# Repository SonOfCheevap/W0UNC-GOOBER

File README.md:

# W0UNC-GOOBER
Project for W0UNC for making off grid communication nodes

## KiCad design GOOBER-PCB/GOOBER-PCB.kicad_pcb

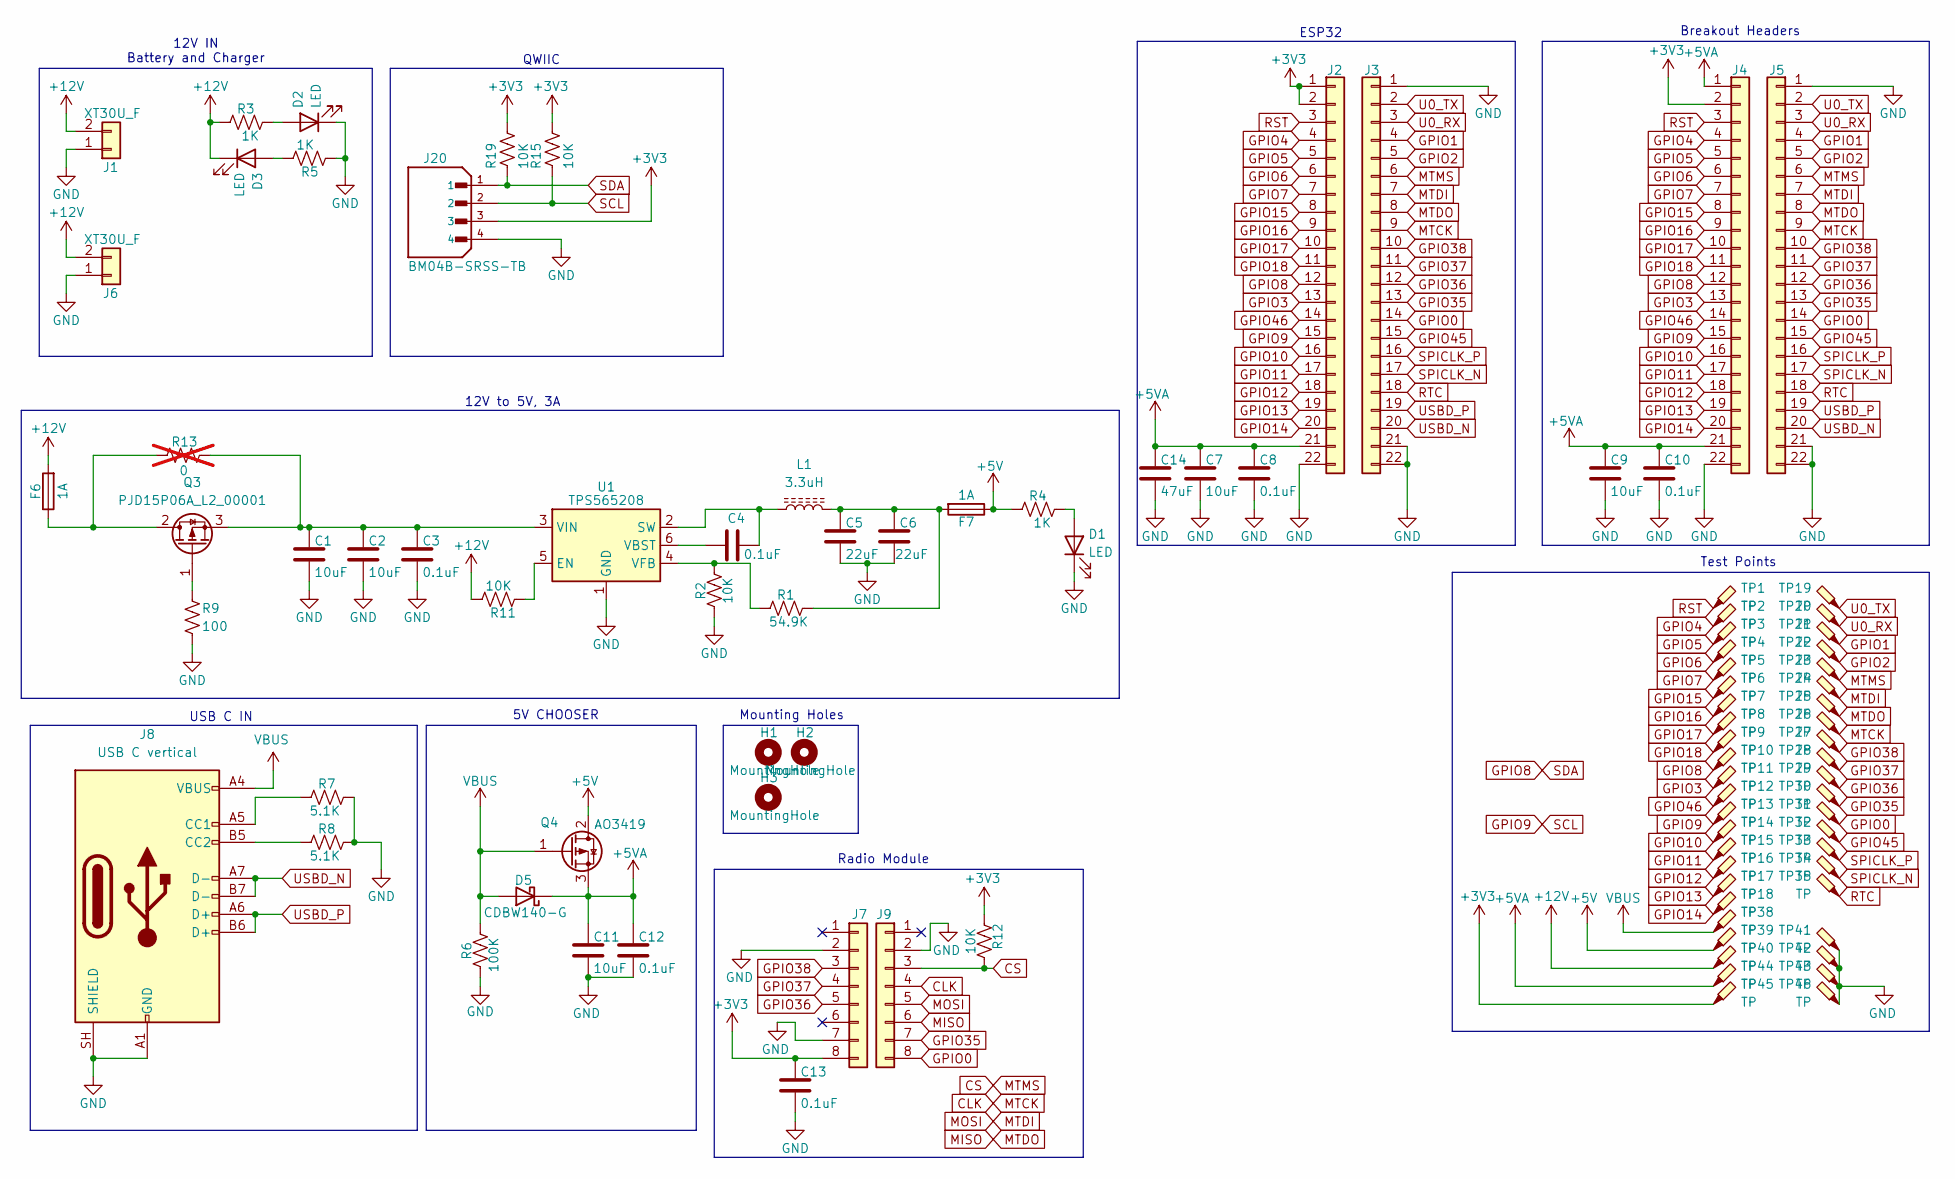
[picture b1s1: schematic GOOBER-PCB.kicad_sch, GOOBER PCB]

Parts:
C1, C2, C7, C9, C11: 10uF; C_0805_2012Metric_Pad1.18x1.45mm_HandSolder
C3, C4, C8, C10, C12, C13: 0.1uF; C_0805_2012Metric_Pad1.18x1.45mm_HandSolder
C5, C6: 22uF; C_0805_2012Metric_Pad1.18x1.45mm_HandSolder
C14: 47uF; C_1206_3216Metric_Pad1.33x1.80mm_HandSolder
D1, D2, D3: LED; LED_0805_2012Metric
D5: CDBW140-G; D_SOD-123
F6, F7: 1A; Fuseholder_Blade_Mini_Keystone_3568
H1, H2, H3: MountingHole; MountingHole_3.2mm_M3_ISO7380
J1, J6: XT30U_F; AMASS_XT30PW-M_1x02_P2.50mm_Horizontal
J2, J3, J4, J5: Conn_01x22; PinHeader_1x22_P2.54mm_Vertical
J7, J9: Conn_01x08; PinHeader_1x08_P2.54mm_Vertical
J8: USB C vertical; USB_C_Receptacle_GCT_USB4115-03-C
J20: BM04B-SRSS-TB; JST_SH_BM04B-SRSS-TB_1x04-1MP_P1.00mm_Vertical; PARTREV NA
L1: 3.3uH; L_TDK_VLS6045EX_VLS6045AF
Q3: PJD15P06A_L2_00001; TO-252-2
Q4: AO3419; SOT-23_Handsoldering
R1: 54.9K; R_0805_2012Metric_Pad1.20x1.40mm_HandSolder
R2, R11, R12, R15, R19: 10K; R_0805_2012Metric_Pad1.20x1.40mm_HandSolder
R3, R4, R5: 1K; R_0805_2012Metric_Pad1.20x1.40mm_HandSolder
R6: 100K; R_0805_2012Metric_Pad1.20x1.40mm_HandSolder
R7, R8: 5.1K; R_0805_2012Metric_Pad1.20x1.40mm_HandSolder
R9: 100; R_0805_2012Metric_Pad1.20x1.40mm_HandSolder
R13: 0; R_1210_3225Metric_Pad1.30x2.65mm_HandSolder; not fitted
TP1, TP2, TP3, TP4, TP5, TP6, TP7, TP8, TP9, TP10, TP11, TP12, TP13, TP14, TP15, TP16, TP17, TP18, TP19, TP20, TP21, TP22, TP23, TP24, TP25, TP26, TP27, TP28, TP29, TP30, TP31, TP32, TP33, TP34, TP35, TP38, TP39, TP40, TP41, TP42, TP43, TP44, TP45, TP46: TP; TestPoint_Keystone_5000-5004_Miniature
U1: TPS565208; SOT-23-6

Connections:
+3V3: C13.1, J2.1, J2.2, J4.2, J7.8, J20.3, R12.1, R15.2, R19.2, TP45.1 (1_1)
+5V: F7.1, Q4.2 (D), R4.1, TP39.1 (1_1)
+5VA: C7.1, C8.1, C9.1, C10.1, C11.1, C12.1, C14.1, D5.1 (K), J2.21, J4.1, J4.21, Q4.3 (S), TP44.1 (1_1)
+12V: D3.1 (K), F6.2, J1.2, J6.2, R3.1, R11.2, TP40.1 (1_1)
CLK: J3.9, J5.9, J9.4, TP26.1 (1_1)
CS: J3.6, J5.6, J9.3, R12.2, TP23.1 (1_1)
GND: C1.2, C2.2, C3.2, C5.2, C6.2, C7.2, C8.2, C9.2, C10.2, C11.2, C12.2, C13.2, C14.2, D1.1 (K), D2.1 (K), J1.1, J2.22, J3.1, J3.21, J3.22, J4.22, J5.1, J5.21, J5.22, J6.1, J7.2, J7.7, J8.A1 (GND), J8.A12 (GND), J8.B1 (GND), J8.B12 (GND), J8.SH (SHIELD), J9.2, J20.4, R2.1, R5.1, R6.1, R7.2, R8.2, R9.2, TP41.1 (1_1), TP42.1 (1_1), TP43.1 (1_1), TP46.1 (1_1), U1.1 (GND)
GPIO0: J3.14, J5.14, J9.8, TP31.1 (1_1)
GPIO1: J3.4, J5.4, TP21.1 (1_1)
GPIO2: J3.5, J5.5, TP22.1 (1_1)
GPIO3: J2.13, J4.13, TP11.1 (1_1)
GPIO4: J2.4, J4.4, TP2.1 (1_1)
GPIO5: J2.5, J4.5, TP3.1 (1_1)
GPIO6: J2.6, J4.6, TP4.1 (1_1)
GPIO7: J2.7, J4.7, TP5.1 (1_1)
GPIO8: J2.12, J4.12, J20.1, R19.1, TP10.1 (1_1)
GPIO9: J2.15, J4.15, J20.2, R15.1, TP13.1 (1_1)
GPIO10: J2.16, J4.16, TP14.1 (1_1)
GPIO11: J2.17, J4.17, TP15.1 (1_1)
GPIO12: J2.18, J4.18, TP16.1 (1_1)
GPIO13: J2.19, J4.19, TP17.1 (1_1)
GPIO14: J2.20, J4.20, TP18.1 (1_1)
GPIO15: J2.8, J4.8, TP6.1 (1_1)
GPIO16: J2.9, J4.9, TP7.1 (1_1)
GPIO17: J2.10, J4.10, TP8.1 (1_1)
GPIO18: J2.11, J4.11, TP9.1 (1_1)
GPIO35: J3.13, J5.13, J9.7, TP30.1 (1_1)
GPIO36: J3.12, J5.12, J7.5, TP29.1 (1_1)
GPIO37: J3.11, J5.11, J7.4, TP28.1 (1_1)
GPIO38: J3.10, J5.10, J7.3, TP27.1 (1_1)
GPIO45: J3.15, J5.15, TP32.1 (1_1)
GPIO46: J2.14, J4.14, TP12.1 (1_1)
MISO: J3.8, J5.8, J9.6, TP25.1 (1_1)
MOSI: J3.7, J5.7, J9.5, TP24.1 (1_1)
unnamed: C5.1, C6.1, F7.2, L1.2, R1.2
unnamed: D1.2 (A), R4.2
unnamed: D2.2 (A), R3.2
unnamed: D3.2 (A), R5.2
unnamed: J8.A5 (CC1), R7.1
unnamed: J8.B5 (CC2), R8.1
unnamed: F6.1, Q3.2 (D), R13.2
unnamed: Q3.1 (G), R9.1
unnamed: C1.1, C2.1, C3.1, Q3.3 (S), R13.1, U1.3 (VIN)
unnamed: R11.1, U1.5 (EN)
unnamed: C4.2, L1.1, U1.2 (SW)
unnamed: C4.1, U1.6 (VBST)
unnamed: R1.1, R2.2, U1.4 (VFB)
RST: J2.3, J4.3, TP1.1 (1_1)
RTC: J3.18, J5.18, TP35.1 (1_1)
SPICLK_N: J3.17, J5.17, TP34.1 (1_1)
SPICLK_P: J3.16, J5.16, TP33.1 (1_1)
U0_RX: J3.3, J5.3, TP20.1 (1_1)
U0_TX: J3.2, J5.2, TP19.1 (1_1)
USBD_N: J3.20, J5.20, J8.A7 (D-), J8.B7 (D-)
USBD_P: J3.19, J5.19, J8.A6 (D+), J8.B6 (D+)
VBUS: D5.2 (A), J8.A4 (VBUS), J8.A9 (VBUS), J8.B4 (VBUS), J8.B9 (VBUS), Q4.1 (G), R6.2, TP38.1 (1_1)

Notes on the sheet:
5V CHOOSER
QWIIC
Breakout Headers
12V to 5V, 3A
ESP32
Radio Module
12V IN Battery and Charger
USB C IN
Mounting Holes
Test Points

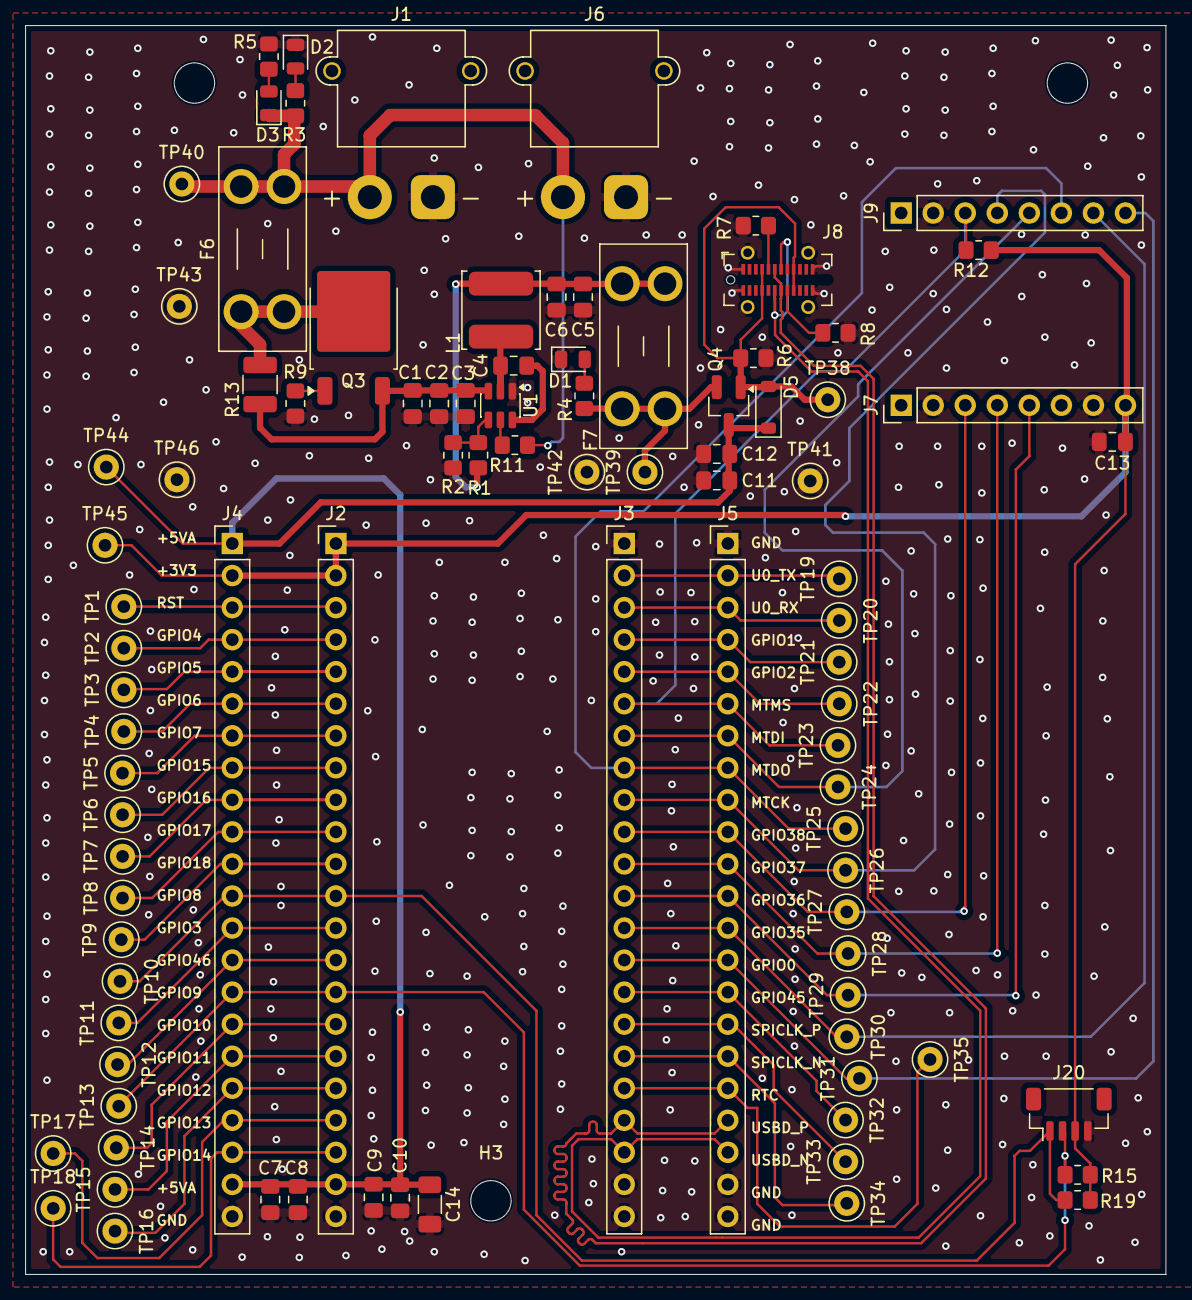
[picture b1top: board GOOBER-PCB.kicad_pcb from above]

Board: 2 copper layers, 90.4 x 99.0 mm, 95 parts (0 on the bottom side), 56 nets.

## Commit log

2026-03-05 created skeleton project
2026-03-20 worked on adding 12v to 5v
2026-04-03 did a lot of work for schematic
2026-04-14 did some layout
2026-04-17 some work on pcb
2026-04-18 first revision of goober pcb
2026-04-21 added 47uF cap
2026-04-24 schematic
